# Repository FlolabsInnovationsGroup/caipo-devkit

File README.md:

# Caipo DEV KIT

Monorepo for the **Caipo DEV KIT**  — a dual-MCU device built from an **ESP32-S3** (always-on power management, sensors, user input) and a **Raspberry Pi** (camera, audio, AI, connectivity), joined by a UART protocol.

Everything ships together in one repo on purpose: the firmware, the Pi software, and the UART protocol that joins them live side by side so a protocol change updates both sides in one atomic commit. The hardware design lives here too, so a pin change and the firmware that uses that pin move together.

## Repository layout

| Directory | Contents | Status |
|---|---|---|
| [`firmware/`](firmware/) | ESP32-S3 firmware (ESP-IDF, C) — see its [README](firmware/README.md) | scaffolded |
| `software/` | Raspberry Pi software (Python package `caipo_pi`) | planned |
| `protocol/` | Single source of truth for the UART contract (`caipo.protocol.yaml` + codegen + golden test vectors) | planned |
| `hardware/` | KiCad schematic, PCB, BOM, datasheets | planned |
| `docs/` | Architecture docs, runbooks, ADRs, and the canonical pin map (`PINMAP.md`) | planned |
| `tools/` | Cross-side scripts: protocol codegen, flash-all, release | planned |
| `.github/` | CI workflows (path-filtered per side), CODEOWNERS, templates | planned |

## Key conventions

- **The protocol is generated, never hand-edited.** `protocol/caipo.protocol.yaml` defines every message once; codegen emits the C codec into `firmware/components/caipo_protocol/` and the Python codec into `software/src/caipo_pi/comm/protocol.py`. Both sides test against the same golden vectors in `protocol/vectors/`, and CI fails if either committed copy drifts.
- **Exactly one place defines a pin.** `docs/PINMAP.md` is the human source of truth; `firmware/components/caipo_bsp/include/caipo_pins.h` must match it.
- **One device version.** A single semver in `VERSION` covers firmware + software + protocol; releases are one tag.
- **Trunk-based development** — short-lived feature branches, protected `main`.
- **Secrets never in git.** WiFi/cloud keys go in encrypted NVS on the ESP and an env file or secrets store on the Pi, provisioned at flash time.

## Quick start

### Firmware (ESP32-S3)

Requires ESP-IDF v5.5.x. From `firmware/`:

```sh
idf.py set-target esp32s3
idf.py build
idf.py -p <PORT> flash monitor
```

See [`firmware/README.md`](firmware/README.md) for details.

### Pi software / protocol / hardware

Not yet in the repo — see the layout table above for where each will land.

## License

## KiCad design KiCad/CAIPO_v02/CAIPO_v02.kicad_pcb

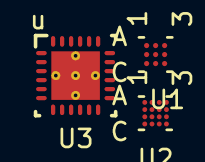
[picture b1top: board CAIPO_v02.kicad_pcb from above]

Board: 2 copper layers, 3 parts (0 on the bottom side), 2 nets, no tracks yet.

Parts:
U1: BQ27427YZFR; BQ27427-YZF_TEX
U2: TPS61290YGB; TPS61290-YBG_TEX
U3: BQ25895RTWR; BQ25895-RTW_TEX

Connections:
unnamed: U1.A3 (VSS_A3), U3.13 (BAT)
unnamed: U2.B2 (VOUT_B2), U3.19 (SW)
